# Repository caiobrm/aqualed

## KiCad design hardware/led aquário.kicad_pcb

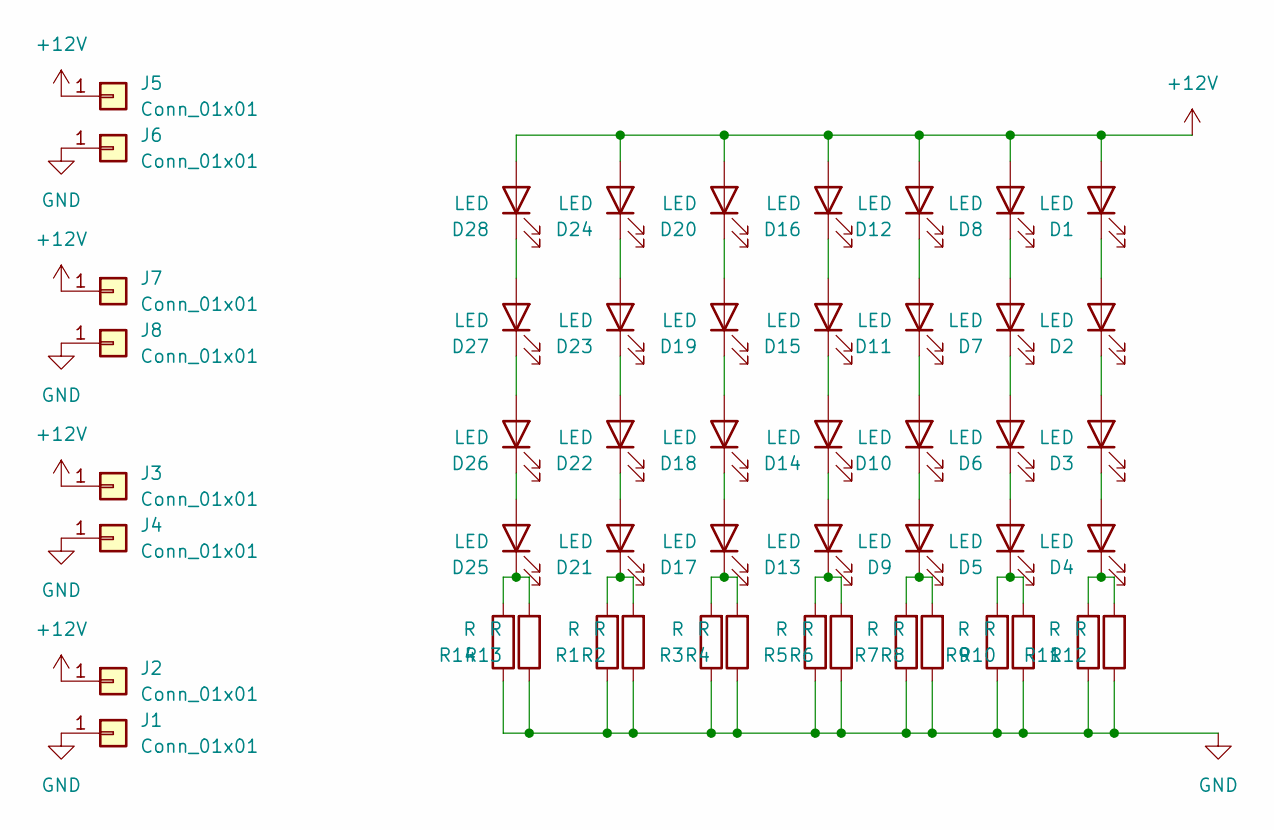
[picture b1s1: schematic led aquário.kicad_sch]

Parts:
D1, D2, D3, D4, D5, D6, D7, D8, D9, D10, D11, D12, D13, D14, D15, D16, D17, D18, D19, D20, D21, D22, D23, D24, D25, D26, D27, D28: LED; Lumex-SML-LXL8047USBCTR3-MFG
J1, J2, J3, J4, J5, J6, J7, J8: Conn_01x01; TestPoint_Pad_4.0x4.0mm
R1, R2, R3, R4, R5, R6, R7, R8, R9, R10, R11, R12, R13, R14: R; R_2512_6332Metric

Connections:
+12V: D1.2 (A), D8.2 (A), D12.2 (A), D16.2 (A), D20.2 (A), D24.2 (A), D28.2 (A), J2.1, J3.1, J5.1, J7.1
GND: J1.1, J4.1, J6.1, J8.1, R1.1, R2.1, R3.1, R4.1, R5.1, R6.1, R7.1, R8.1, R9.1, R10.1, R11.1, R12.1, R13.1, R14.1
unnamed: D1.1 (K), D2.2 (A)
unnamed: D2.1 (K), D3.2 (A)
unnamed: D3.1 (K), D4.2 (A)
unnamed: D4.1 (K), R11.2, R12.2
unnamed: D5.2 (A), D6.1 (K)
unnamed: D5.1 (K), R9.2, R10.2
unnamed: D6.2 (A), D7.1 (K)
unnamed: D7.2 (A), D8.1 (K)
unnamed: D9.1 (K), R7.2, R8.2
unnamed: D10.2 (A), D11.1 (K)
unnamed: D9.2 (A), D10.1 (K)
unnamed: D11.2 (A), D12.1 (K)
unnamed: D13.2 (A), D14.1 (K)
unnamed: D13.1 (K), R5.2, R6.2
unnamed: D14.2 (A), D15.1 (K)
unnamed: D15.2 (A), D16.1 (K)
unnamed: D17.2 (A), D18.1 (K)
unnamed: D17.1 (K), R3.2, R4.2
unnamed: D18.2 (A), D19.1 (K)
unnamed: D19.2 (A), D20.1 (K)
unnamed: D21.2 (A), D22.1 (K)
unnamed: D21.1 (K), R1.2, R2.2
unnamed: D22.2 (A), D23.1 (K)
unnamed: D23.2 (A), D24.1 (K)
unnamed: D25.2 (A), D26.1 (K)
unnamed: D25.1 (K), R13.2, R14.2
unnamed: D26.2 (A), D27.1 (K)
unnamed: D27.2 (A), D28.1 (K)

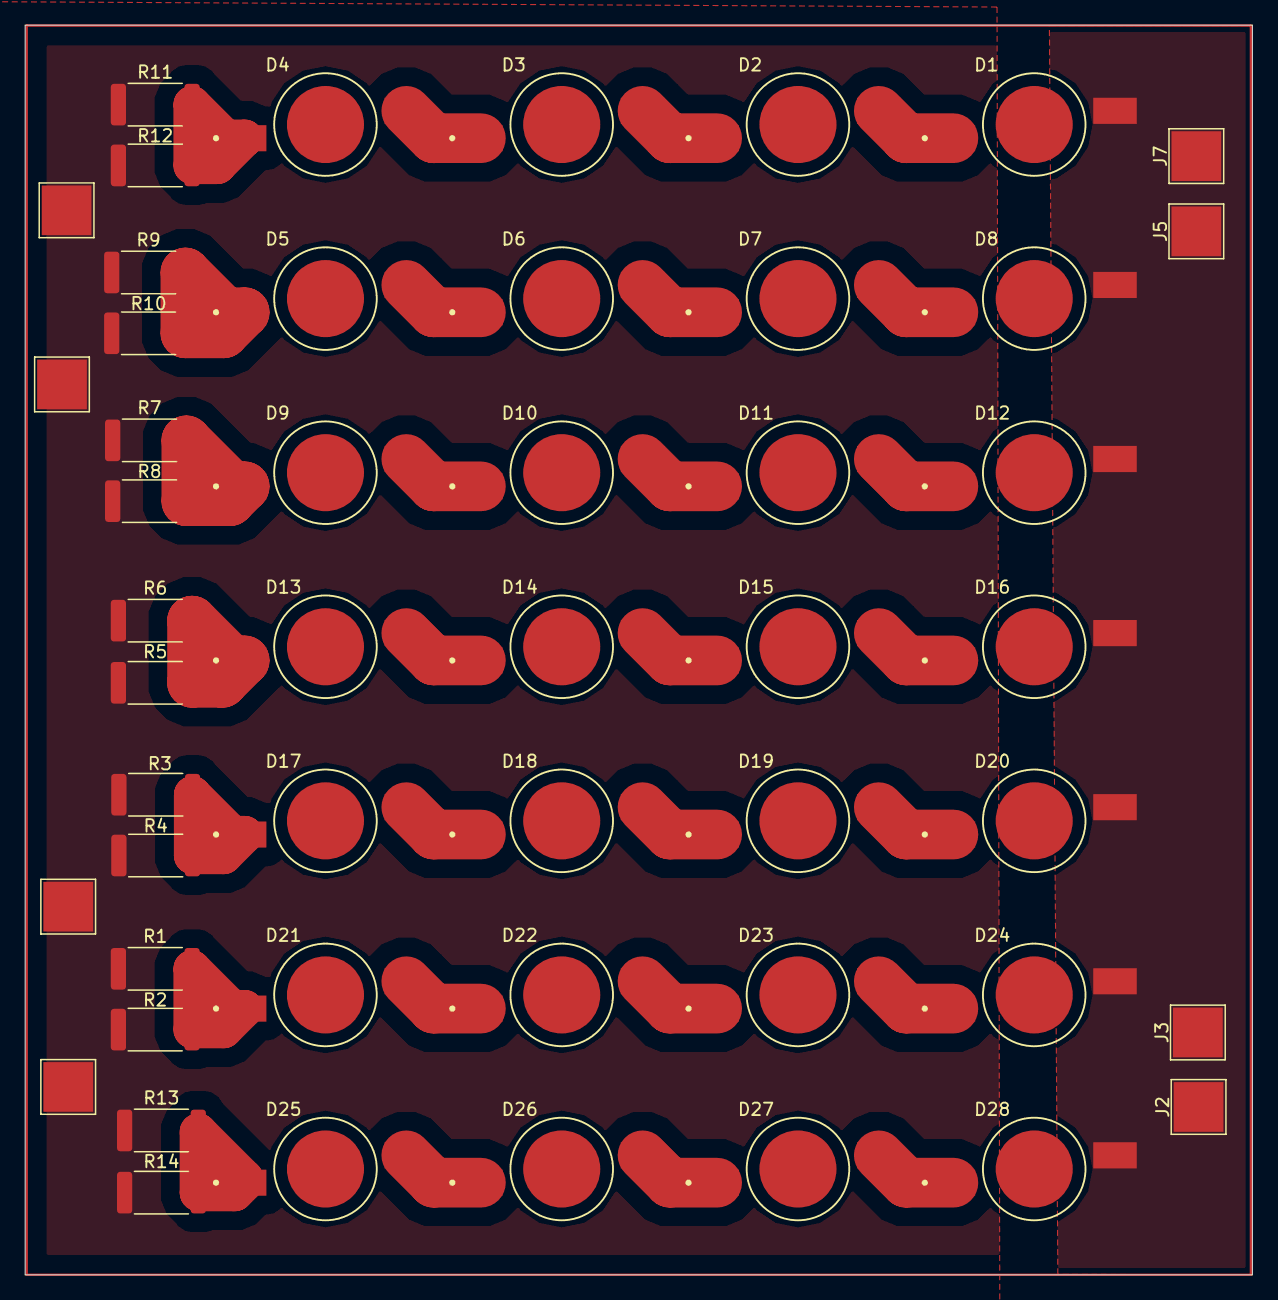
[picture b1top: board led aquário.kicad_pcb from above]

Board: 2 copper layers, 98.7 x 100.5 mm, 50 parts (0 on the bottom side), 30 nets.
